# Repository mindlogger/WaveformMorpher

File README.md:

# WaveformMorpher
Morphing wavetable Synthesizer based on a Raspberry Pi.
Dependencies:
>= Portaudio v190600_20161030
https://github.com/grz0zrg/fbg
https://github.com/nlohmann/json
http://www.fftw.org/
https://github.com/thestk/rtmidi

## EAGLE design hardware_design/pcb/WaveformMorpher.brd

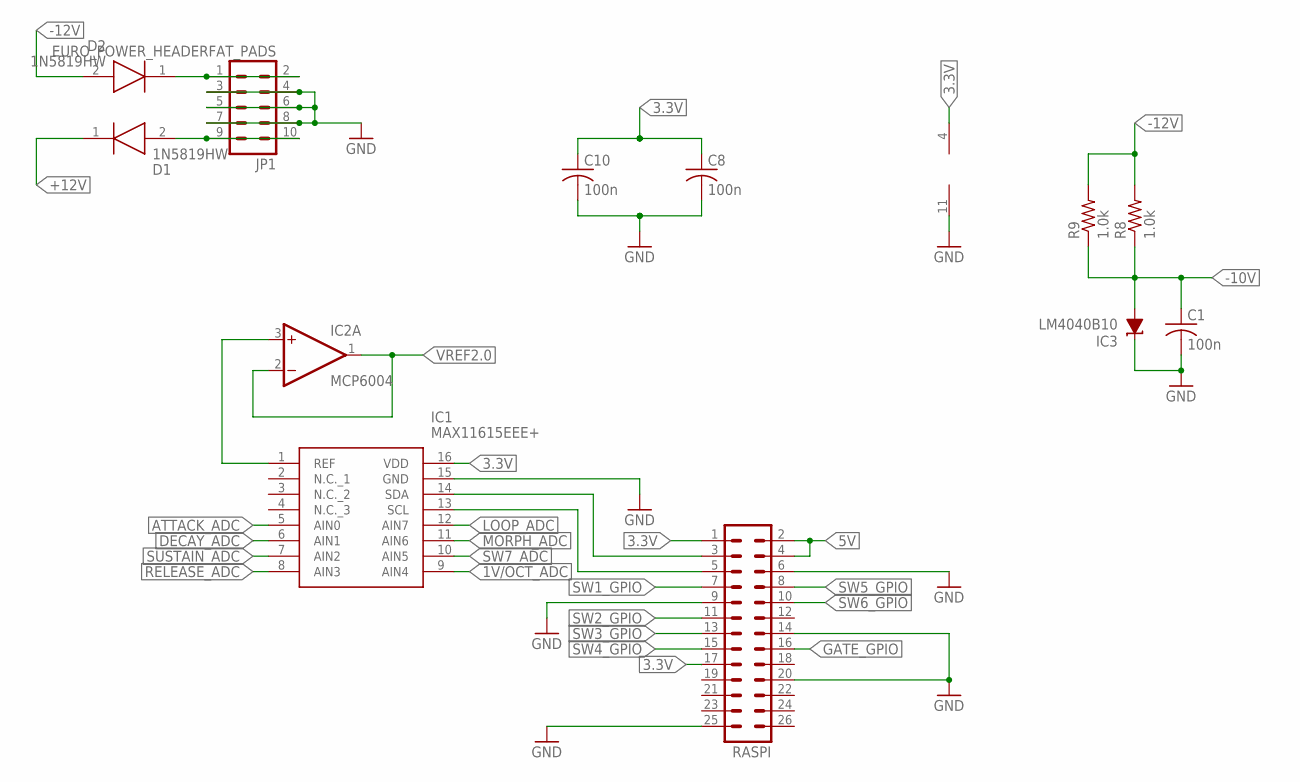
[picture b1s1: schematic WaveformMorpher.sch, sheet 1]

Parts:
C1, C8, C10: 100n; C0603
D1, D2: 1N5819HW; SOD3716X145N
IC1: MAX11615EEE+; SOP64P602X175-16N
IC2: MCP6004; SO14
IC3: LM4040B10; DBZ_R-PDSO-G3
JP1: EURO_POWER_HEADERFAT_PADS; EURO_PWR_HEADER_FAT
R8, R9: 1.0k; R0603
RASPI: MA13-2

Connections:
1V/OCT_ADC: IC1.9 (AIN4); also elsewhere on the board
3.3V: C8.1, C10.1, IC1.16 (VDD), IC2.4 (V+), RASPI.1, RASPI.17; also elsewhere on the board
5V: RASPI.2, RASPI.4; also elsewhere on the board
+12V: D1.1 (K); also elsewhere on the board
-10V: C1.1, IC3.2 (A), R8.1, R9.1; also elsewhere on the board
-12V: D2.2 (A), R8.2, R9.2; also elsewhere on the board
ATTACK_ADC: IC1.5 (AIN0); also elsewhere on the board
DECAY_ADC: IC1.6 (AIN1); also elsewhere on the board
GATE_GPIO: RASPI.16; also elsewhere on the board
GND: C1.2, C8.2, C10.2, IC1.15 (GND), IC2.11 (V-), IC3.1 (C), JP1.3, JP1.4, JP1.5, JP1.6, JP1.7, JP1.8, RASPI.6, RASPI.9, RASPI.14, RASPI.20, RASPI.25; also elsewhere on the board
LOOP_ADC: IC1.12 (AIN7); also elsewhere on the board
MORPH_ADC: IC1.11 (AIN6); also elsewhere on the board
unnamed: IC1.14 (SDA), RASPI.3
unnamed: IC1.1 (REF), IC2.3 (+IN)
unnamed: IC1.13 (SCL), RASPI.5
unnamed: D2.1 (K), JP1.1, JP1.2
unnamed: D1.2 (A), JP1.9, JP1.10
RELEASE_ADC: IC1.8 (AIN3); also elsewhere on the board
SUSTAIN_ADC: IC1.7 (AIN2); also elsewhere on the board
SW1_GPIO: RASPI.7; also elsewhere on the board
SW2_GPIO: RASPI.11; also elsewhere on the board
SW3_GPIO: RASPI.13; also elsewhere on the board
SW4_GPIO: RASPI.15; also elsewhere on the board
SW5_GPIO: RASPI.8; also elsewhere on the board
SW6_GPIO: RASPI.10; also elsewhere on the board
SW7_ADC: IC1.10 (AIN5); also elsewhere on the board
VREF2.0: IC2.1 (OUT), IC2.2 (-IN); also elsewhere on the board

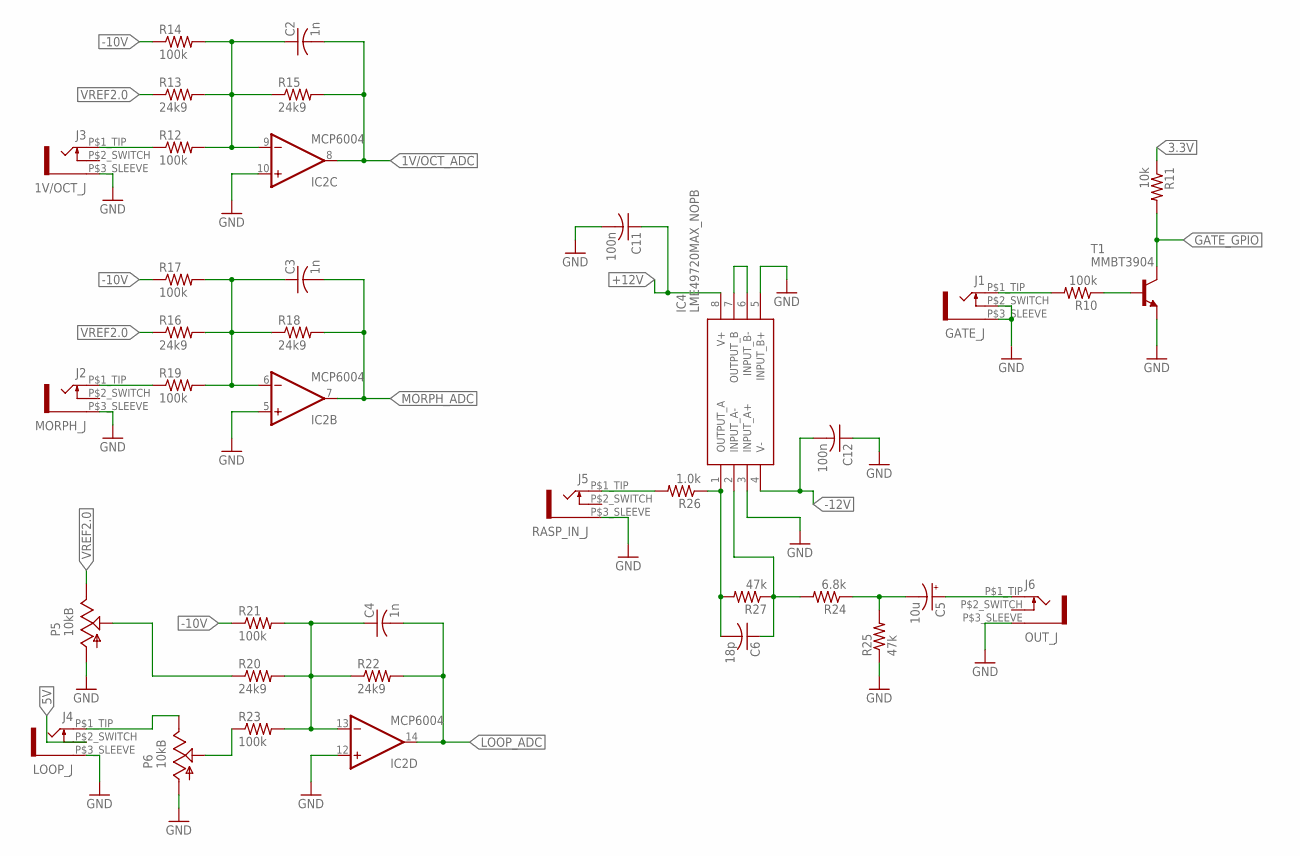
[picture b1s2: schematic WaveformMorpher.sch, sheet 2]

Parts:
C2, C3, C4: 1n; C0603
C5: 10u; PANASONIC_B
C6: 18p; C0603
C11, C12: 100n; C0603
IC2: MCP6004; SO14
IC4: LME49720MAX_NOPB; SOIC127P600X175-8N
J1: GATE_J; WQP-PJ301M-12_JACK
J2: MORPH_J; WQP-PJ301M-12_JACK
J3: 1V/OCT_J; WQP-PJ301M-12_JACK
J4: LOOP_J; WQP-PJ301M-12_JACK
J5: RASP_IN_J; WQP-PJ301M-12_JACK
J6: OUT_J; WQP-PJ301M-12_JACK
P5, P6: 10kB; 9MM_SNAP-IN_POT
R10, R12, R14, R17, R19, R21, R23: 100k; R0603
R11: 10k; R0603
R13, R15, R16, R18, R20, R22: 24k9; R0603
R24: 6.8k; R0603
R25, R27: 47k; R0603
R26: 1.0k; R0603
T1: MMBT3904; SOT23-BEC

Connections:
1V/OCT_ADC: C2.2, IC2.8 (OUT), R15.2; also elsewhere on the board
3.3V: R11.1; also elsewhere on the board
5V: J4.P$2_SWITCH (3); also elsewhere on the board
+12V: C11.1, IC4.8 (V+); also elsewhere on the board
-10V: R14.1, R17.1, R21.1; also elsewhere on the board
-12V: C12.2, IC4.4 (V-); also elsewhere on the board
GATE_GPIO: R11.2, T1.C; also elsewhere on the board
GND: C11.2, C12.1, IC2.5 (+IN), IC2.10 (+IN), IC2.12 (+IN), IC4.3 (INPUT_A+), IC4.5 (INPUT_B+), J1.P$2_SWITCH (3), J1.P$3_SLEEVE (1), J2.P$3_SLEEVE (1), J3.P$3_SLEEVE (1), J4.P$3_SLEEVE (1), J5.P$3_SLEEVE (1), J6.P$3_SLEEVE (1), P5.1 (A), P6.1 (A), R25.1, T1.E; also elsewhere on the board
LOOP_ADC: C4.2, IC2.14 (OUT), R22.2; also elsewhere on the board
MORPH_ADC: C3.2, IC2.7 (OUT), R18.2; also elsewhere on the board
unnamed: J1.P$1_TIP (2), R10.2
unnamed: R10.1, T1.B
unnamed: J2.P$1_TIP (2), R19.1
unnamed: C2.1, IC2.9 (-IN), R12.2, R13.2, R14.2, R15.1
unnamed: C3.1, IC2.6 (-IN), R16.2, R17.2, R18.1, R19.2
unnamed: J3.P$1_TIP (2), R12.1
unnamed: C4.1, IC2.13 (-IN), R20.2, R21.2, R22.1, R23.2
unnamed: J4.P$1_TIP (2), P6.3 (E)
unnamed: IC4.6 (INPUT_B-), IC4.7 (OUTPUT_B)
unnamed: C6.2, IC4.1 (OUTPUT_A), R26.1, R27.2
unnamed: J5.P$1_TIP (2), R26.2
unnamed: C5.+, J6.P$1_TIP (2)
unnamed: C5.-, R24.1, R25.2
unnamed: P5.2 (S), R20.1
unnamed: C6.1, IC4.2 (INPUT_A-), R24.2, R27.1
unnamed: P6.2 (S), R23.1
VREF2.0: P5.3 (E), R13.1, R16.1; also elsewhere on the board

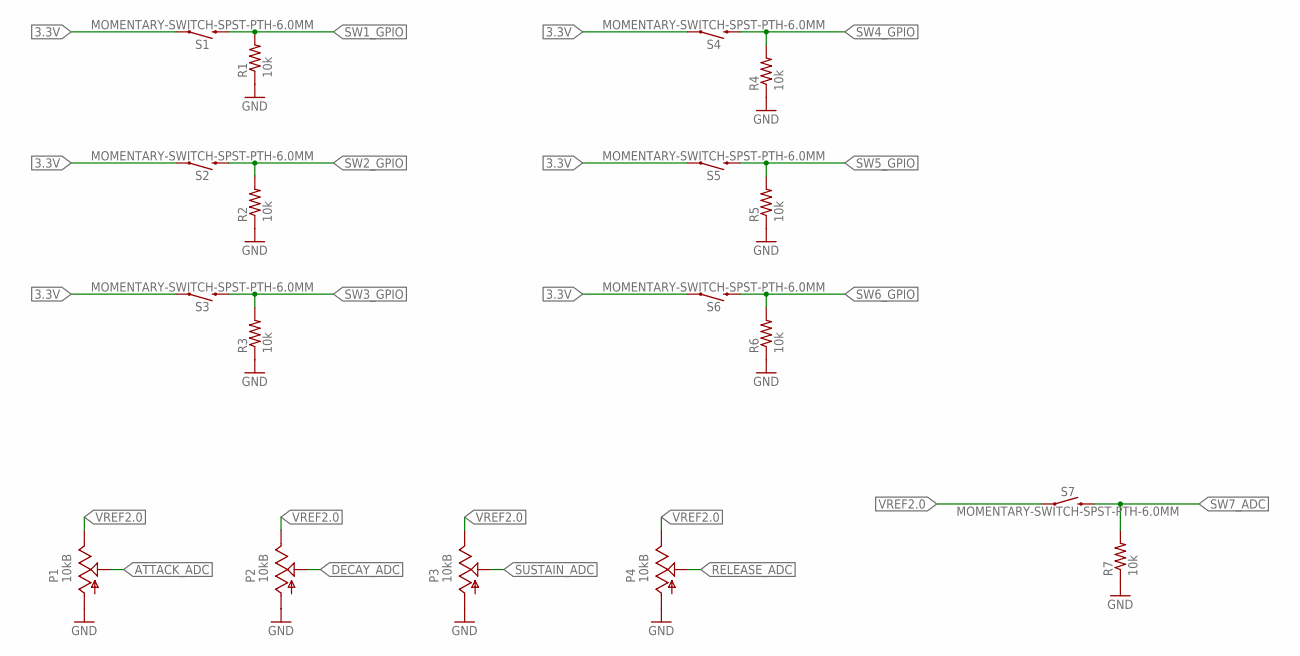
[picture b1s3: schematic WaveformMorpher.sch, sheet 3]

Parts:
P1, P2, P3, P4: 10kB; 9MM_SNAP-IN_POT
R1, R2, R3, R4, R5, R6, R7: 10k; R0603
S1, S2, S3, S4, S5, S6, S7: MOMENTARY-SWITCH-SPST-PTH-6.0MM; TACTILE_SWITCH_PTH_6.0MM

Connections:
3.3V: S1.1, S2.1, S3.1, S4.1, S5.1, S6.1; also elsewhere on the board
ATTACK_ADC: P1.2 (S); also elsewhere on the board
DECAY_ADC: P2.2 (S); also elsewhere on the board
GND: P1.1 (A), P2.1 (A), P3.1 (A), P4.1 (A), R1.1, R2.1, R3.1, R4.1, R5.1, R6.1, R7.1; also elsewhere on the board
RELEASE_ADC: P4.2 (S); also elsewhere on the board
SUSTAIN_ADC: P3.2 (S); also elsewhere on the board
SW1_GPIO: R1.2, S1.3 (2); also elsewhere on the board
SW2_GPIO: R2.2, S2.3 (2); also elsewhere on the board
SW3_GPIO: R3.2, S3.3 (2); also elsewhere on the board
SW4_GPIO: R4.2, S4.3 (2); also elsewhere on the board
SW5_GPIO: R5.2, S5.3 (2); also elsewhere on the board
SW6_GPIO: R6.2, S6.3 (2); also elsewhere on the board
SW7_ADC: R7.2, S7.3 (2); also elsewhere on the board
VREF2.0: P1.3 (E), P2.3 (E), P3.3 (E), P4.3 (E), S7.1; also elsewhere on the board

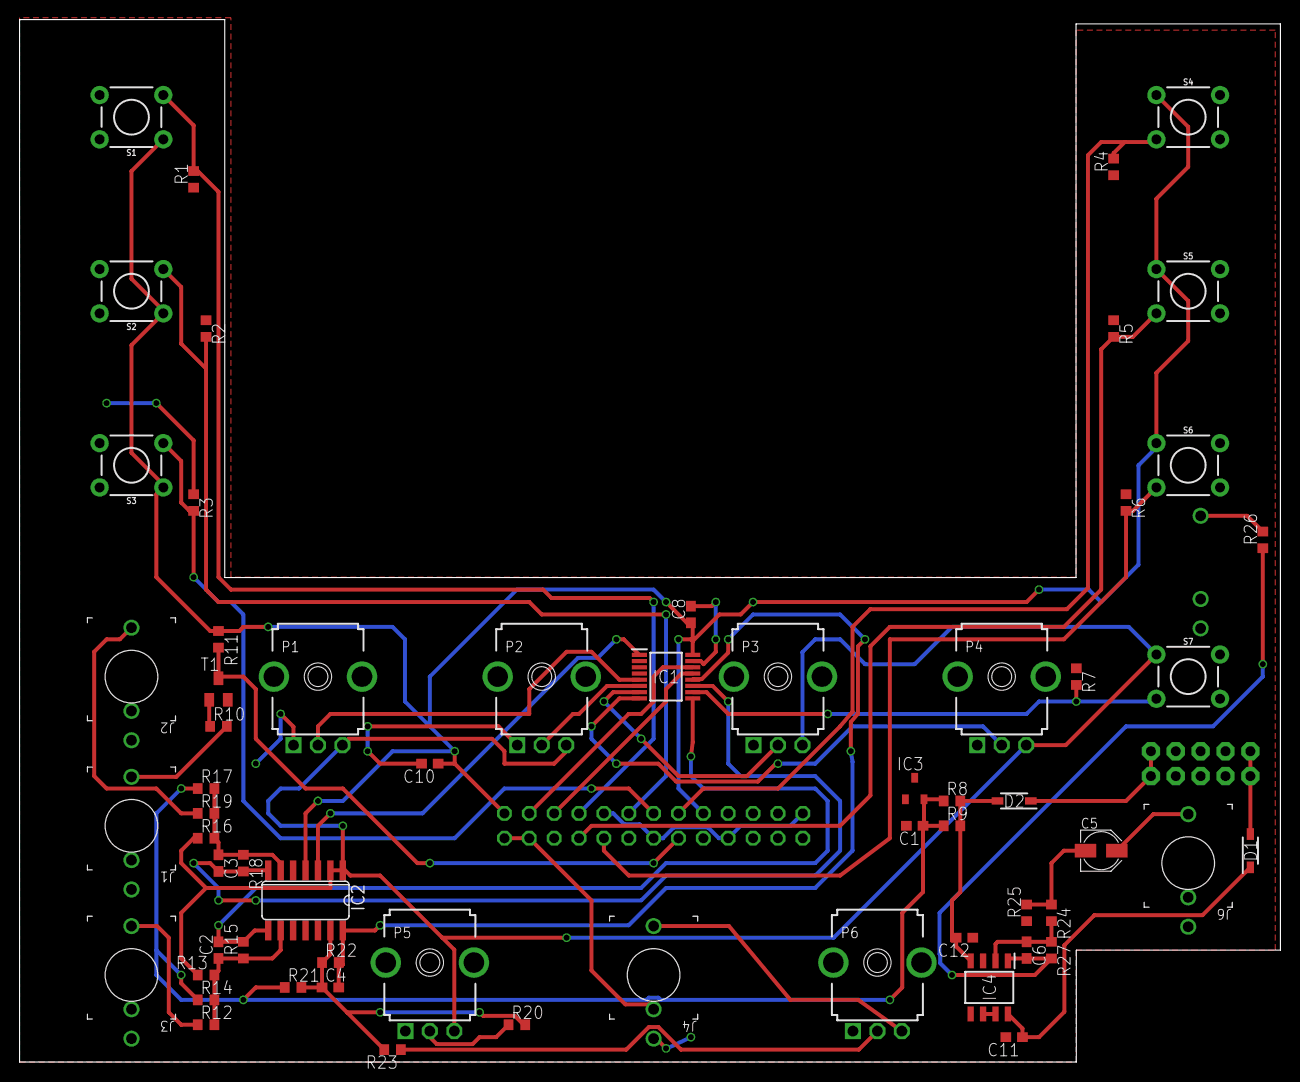
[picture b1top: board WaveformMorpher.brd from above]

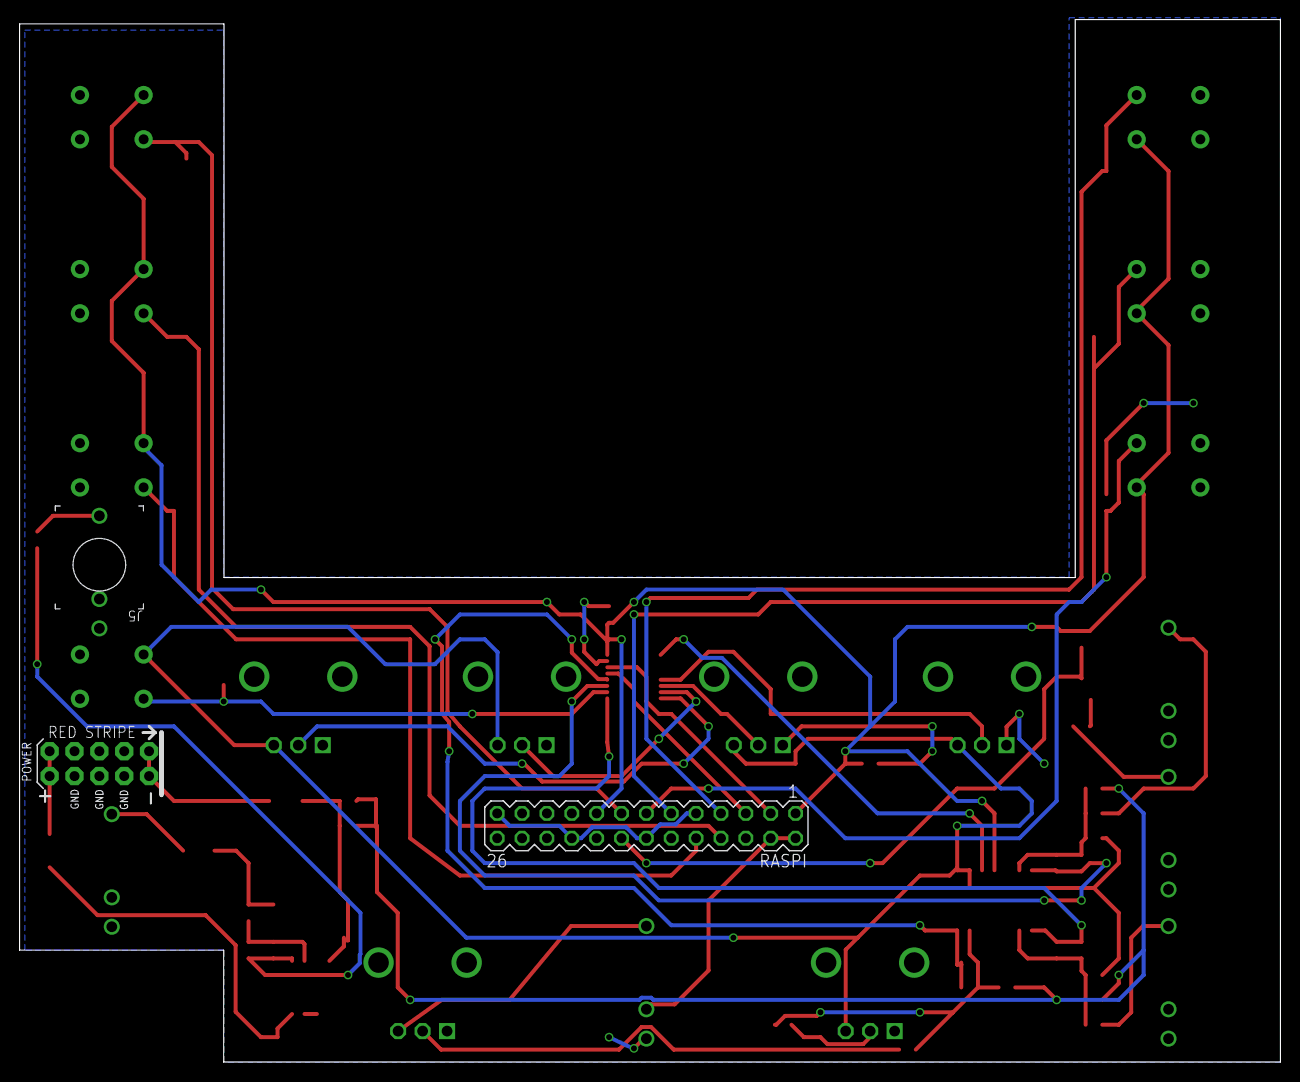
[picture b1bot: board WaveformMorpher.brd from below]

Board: 2 copper layers, 128.8 x 106.5 mm, 65 parts (3 on the bottom side), 43 nets.

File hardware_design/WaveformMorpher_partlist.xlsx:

Waveform Morpher v0.7
Qty | Parts | Value | Package | Device | Description | DESCRIPTION.1 | HEIGHT | MANUFACTURER_NAME | MANUFACTURER_PART_NUMBER | MF | MOUSER_PART_NUMBER | MOUSER_PRICE-STOCK | MPN | OC_FARNELL | OC_NEWARK | PROD_ID | RS_PART_NUMBER | RS_PRICE-STOCK | SF_SKU | Column1
3 | R8, R9, R26 | 1.0k | R0603 | R-US_R0603 | RESISTOR, American symbol
7 | R10, R12, R14, R17, R19, R21, R23 | 100k | R0603 | R-US_R0603 | RESISTOR, American symbol
5 | C1, C8, C10, C11, C12 | 100n | C0603 | C-USC0603 | CAPACITOR, American symbol
8 | R1, R2, R3, R4, R5, R6, R7, R11 | 10k | R0603 | R-US_R0603 | RESISTOR, American symbol
6 | P1, P2, P3, P4, P5, P6 | 10kB | 9MM_SNAP-IN_POT | 9MM_SNAP-IN_POT_ | 9mm vertical snap-in pot, Alpha / Panasonic style
1 | C5 | 10u | PANASONIC_B | CPOL-USB | POLARIZED CAPACITOR, American symbol
1 | C6 | 18p | C0603 | C-USC0603 | CAPACITOR, American symbol
3 | C2, C3, C4 | 1n | C0603 | C-USC0603 | CAPACITOR, American symbol
6 | R13, R15, R16, R18, R20, R22 | 24k9 | R0603 | R-US_R0603 | RESISTOR, American symbol
2 | R25, R27 | 47k | R0603 | R-US_R0603 | RESISTOR, American symbol
1 | R24 | 6.8k | R0603 | R-US_R0603 | RESISTOR, American symbol
1 | T1 | MMBT3904 | SOT23-BEC | MMBT3904LT1-NPN-SOT23-BEC | NPN Transistror
2 | D1, D2 | 1N5819HW | SOD3716X145N | 1N5819HW | 1.0A SURFACE MOUNT SCHOTTKY BARRIER RECTIFIER | 1.0A SURFACE MOUNT SCHOTTKY BARRIER RECTIFIER | 1.45mm | Diodes Inc. | 1N5819HW
1 | IC1 | MAX11615EEE+ | SOP64P602X175-16N | MAX11615EEE+ | IC,ADC,MAX11615EEE+ Maxim MAX11615EEE+, 12 bit Parallel ADC, 8-channel Differen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 | IC,ADC,MAX11615EEE+ Maxim MAX11615EEE+, 12 bit Parallel ADC, 8-channel Differen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 | 1.75mm | Maxim Integrated | MAX11615EEE+ |  | 700-MAX11615EEE | https://www.mouser.com/Search/Refine.aspx?Keyword=700-MAX11615EEE
1 | IC2 | MCP6004 | SO14 | TL074D | OP AMP
1 | IC3 | LM4041B12DBZ | DBZ_R-PDSO-G3 | LM4041B12DBZ | PRECISION MICROPOWER SHUNT VOLTAGE REFERENCE |  |  |  |  |  |  |  | LM4041B12IDBZR | 1575212 | 58K5882
1 | IC4 | LME49720MAX_NOPB | SOIC127P600X175-8N | LME49720MAX_NOPB | Dual High Performance, High Fidelity Audio Operational Amplifier | Dual High Performance, High Fidelity Audio Operational Amplifier | 1.75mm | Texas Instruments | LME49720MAX/NOPB |  | 926-LME49720MAX/NOPB | https://www.mouser.com/Search/Refine.aspx?Keyword=926-LME497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
7 | SW1, SW2, SW3, SW4, SW5, SW6, SW7 | MOMENTARY-SWITCH-SPST-PTH-6.0MM | TACTILE_SWITCH_PTH_6.0MM | MOMENTARY-SWITCH-SPST-PTH-6.0MM | Momentary Switch (Pushbutton) - SPST |  |  |  |  |  |  |  |  |  |  | SWCH-08441 |  |  | COM-00097
1 | RASPI |  | MA13-2 | MA13-2 | PIN HEADER
1 | JP1 | EURO_POWER_HEADERFAT_PADS | EURO_PWR_HEADER_FAT | EURO_POWER_HEADERFAT_PADS | Power Header
6 | J1, J2, J3, J4, J5, J6 | Jacks | WQP-PJ301M-12_JACK | WQP-PJ301M-12_JACK
7 | SC1, SC2, SC3, SC4, SC5, SC6, SC7 | Switchcaps
6 | PC1, PC2, PC3, PC4, PC5, PC6 | Potcaps
TH
SM
Other

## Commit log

2020-01-28 basic setup as proof of concept
2020-01-30 basic midi setup
2020-01-30 restructured wavetable
2020-01-31 removed midilib files
2020-01-31 wavetable stable AND timer initial setup
2020-02-01 fourier transform impl AND float to double
2020-02-02 table2screen fixed AND DFT improvements AND terminal control
2020-02-04 FFT IFFT SET UP AND SCALED AND FIRST TRY ON SMOOTHING OUT SCREEN
2020-02-05 basic rounding implemented AND continousScreen fixed
2020-02-05 touchscreen and framebuffer fixes at cost of audio lags
2020-02-07 first take on enum setup for morphing AND first take on touchscreen2spectrum
2020-02-09 added basic gateing AND waveform choices
2020-02-13 BROKEN BUILD BUT FIRST REAL IFFT WITH SPEC EDIT POSSIBLE
2020-02-16 SHIT IFFT IMPL ONLY WORKS WITH ROUNDING
2020-02-17 small general improvements
2020-02-18 global var for wave and fft
2020-02-18 small bugfixes
2020-03-03 added destructors
2020-03-11 setup hardware stuff
2020-03-18 Board added
2020-03-18 Board first placements
2020-03-20 adding vias
2020-03-23 finishing up the board
2020-03-24 hardware v0.7
2020-03-28 partlist and bugfixes
2020-04-02 setting up pointers for wavetables
2020-04-03 touchscreen enhancements
2020-04-04 listclear timer setup
2020-04-08 fbg basic setup
2020-04-09 Basic envelope setup
2020-04-13 screen wavemorphing
2020-04-13 setup ui
2020-04-17 dynamic mode and waveform envelope
2020-04-19 new fft implementation
2020-04-20 removed bin and obj files AND envelope and dyn mode fixes
2020-04-22 partlist excel bugfix
2020-04-26 ADC basic setup
2020-04-26 Removing all files in .gitignore
2020-04-27 envelope looping on screen AND UI stuff
2020-04-27 audio looping setup AND small fixes
2020-05-20 first proper panel layout
2022-08-17 fourier flag visulaized + graphic pages added for settings
2022-08-18 setup json-c library
2022-08-18 btn context with func pointers
2022-08-18 timeoutable text + improved rendering
2022-08-19 added file save
2022-08-19 implemented store screen
2022-08-19 added file reading
2022-08-19 basic file browsing capabilities
2022-08-19 working file browsing saving loading
2022-08-20 improved touchscreen behavior
2022-08-20 fixed dynamic mode and added marker
2022-08-20 implemented basic bluring
2022-08-20 added blur algorithm
2022-08-20 improvements to displaying things
2022-08-20 implemented global preset system
2022-08-20 removed clipboard from patch save
2022-08-20 added option for wave display style
2022-08-20 added little arrows for navigation
2022-08-20 improved wave morphing sound
2022-08-20 implemented vary table sizes
2022-08-21 added other blur algo and added windowing
2022-08-21 improved osc behaviour
2022-08-21 added VCA option
2022-08-21 waveInsertion work in progress
2022-08-21 wave insertion page
2022-08-21 added color + fixed bunch of screen alignment
2022-08-22 added clipping protection
2022-08-22 added knobbehaviour + continous option
2022-08-22 added knobbehaviour to the json saving
2022-08-22 added undo for fft
2022-08-22 linear rates + improved init preset
2022-08-22 wave saving/loading implemented
2022-08-22 blur cueing
2022-08-23 soft takeover work in progress
2022-08-23 soft takeover implemented
2022-08-23 added filter modes
2022-08-23 added arrows and floppy images to browsing
2022-08-23 clean shutdown implemented
2022-08-24 improved midi to gate behaviour
2022-08-24 implemented all notes off
2022-08-24 small typo
2022-08-24 fixed multiple sources of clipping
2022-08-24 added some extra though to the env to wavetable stuff
2022-08-24 fixing audio shit work in progress
2022-08-24 implemented a second envelope and made it all sound nice
2022-08-24 added reboot but commented it out
2022-08-24 tiny hotfix to rendering

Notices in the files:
parts and their libraries:
SparkFun-Switches: Licensing: Creative Commons ShareAlike 4.0 International - https://creativecommons.org/licenses/by-sa/4.0
